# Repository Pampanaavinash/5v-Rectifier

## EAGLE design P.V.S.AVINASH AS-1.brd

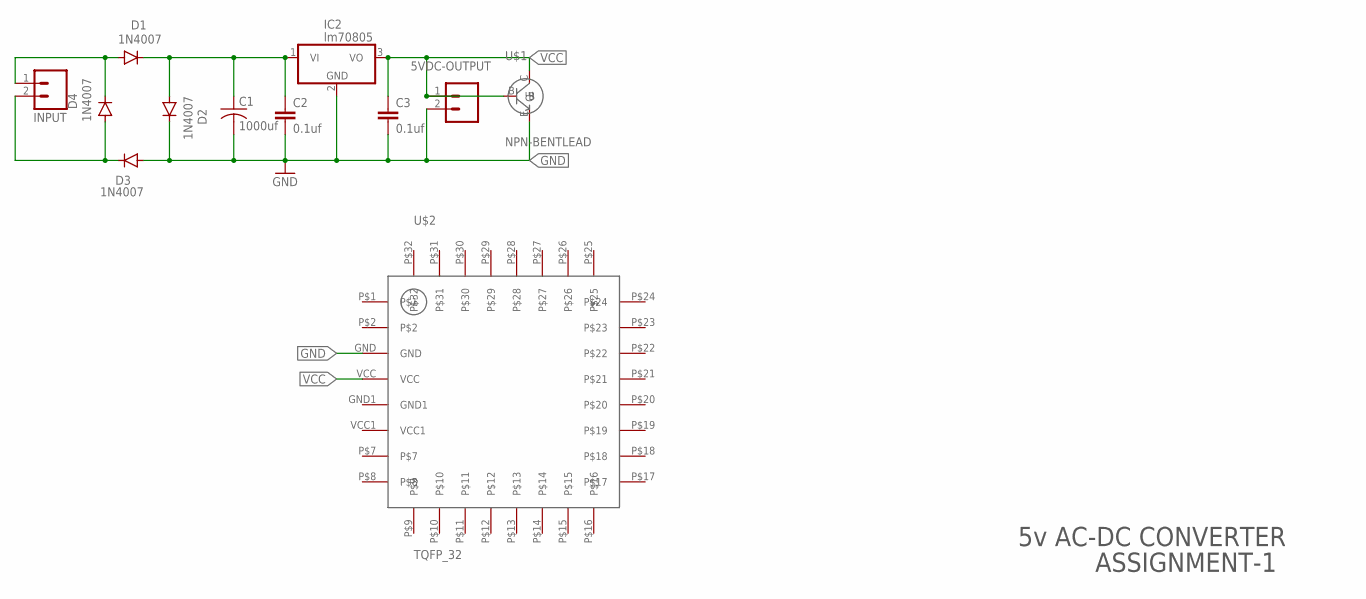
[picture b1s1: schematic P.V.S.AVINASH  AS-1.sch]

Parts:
5VDC-OUTPUT: M02; 02P
C1: 1000uf; C025-024X044
C2, C3: 0.1uf; C025-025X050
D1, D2, D3, D4: 1N4007; DO41-10
IC2: lm70805; TO220V
INPUT: M02; 02P
U$1: NPN-BENTLEAD; BENT-LEAD
U$2: TQFP_32

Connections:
GND: 5VDC-OUTPUT.2, C1.2, C2.2, C3.2, D2.C, D3.A, IC2.2 (GND), U$1.E, U$2.GND
unnamed: D1.A, D4.C, INPUT.1
unnamed: D3.C, D4.A, INPUT.2
unnamed: C1.1, C2.1, D1.C, D2.A, IC2.1 (VI)
VCC: 5VDC-OUTPUT.1, C3.1, IC2.3 (VO), U$1.B, U$1.C, U$2.VCC

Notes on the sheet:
5v AC-DC CONVERTER
ASSIGNMENT-1

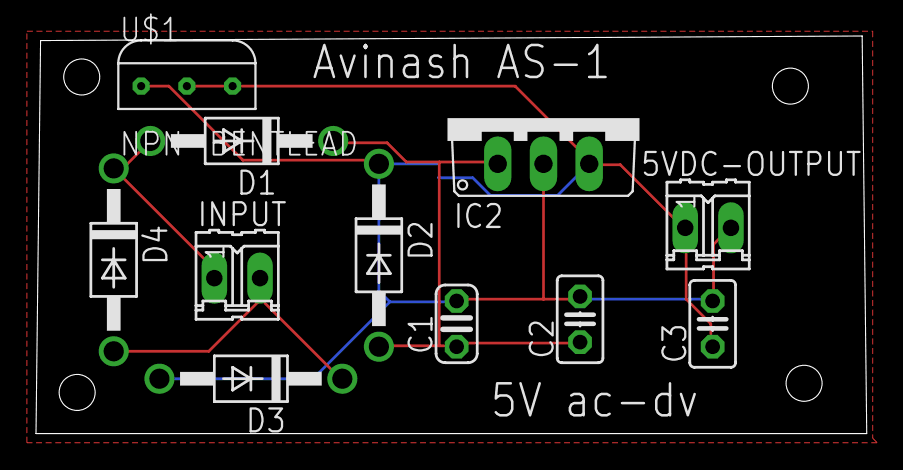
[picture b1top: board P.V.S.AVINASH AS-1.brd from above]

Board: 2 copper layers, 46.2 x 22.1 mm, 12 parts (1 on the bottom side), 5 nets.

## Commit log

2024-02-29 Create 5V AC-DC Gerber Files
2024-02-29 Create 5v AC-DC Gerber Files
2024-02-29 5V AC-DC Gerber Files
